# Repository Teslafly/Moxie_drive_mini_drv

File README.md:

# Moxie_drive_mini_drv
A motor drive based off https://github.com/vedderb/bldc-hardware using the drv8353 and toshiba fets

MoxiE-Drive - high power 12-75v motor controller
=============

design

Forged from the remminants of the oppressed vesc 6.
Raised on a diet of endless sphere and equals zero posts.
destined for a fight to the death in hilariously brutal Power Wheels Racing Series.
I give to you, the MoxiE-Drive.

This the Hardware for my derivitive of the Vesc-project.

## Schematic top level

## Layout -made with KiCad!-

## 3D views

Have a look at this post for a tutorial on how to get started:
http://vedder.se/2015/01/vesc-open-source-esc/

Made with KiCad 5

wonderfulfailure.wordpress.com

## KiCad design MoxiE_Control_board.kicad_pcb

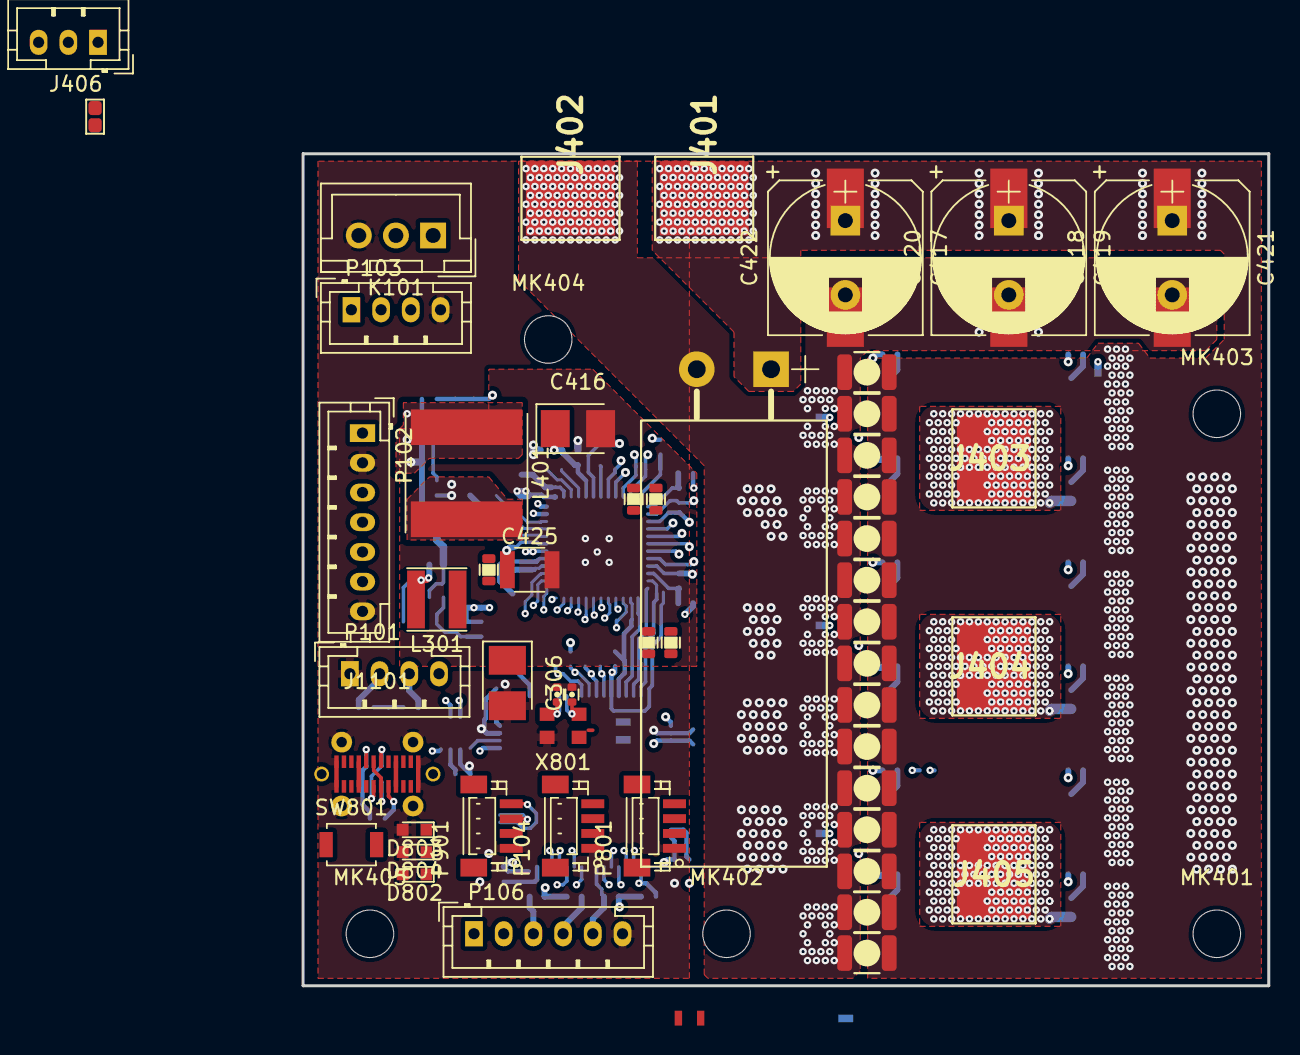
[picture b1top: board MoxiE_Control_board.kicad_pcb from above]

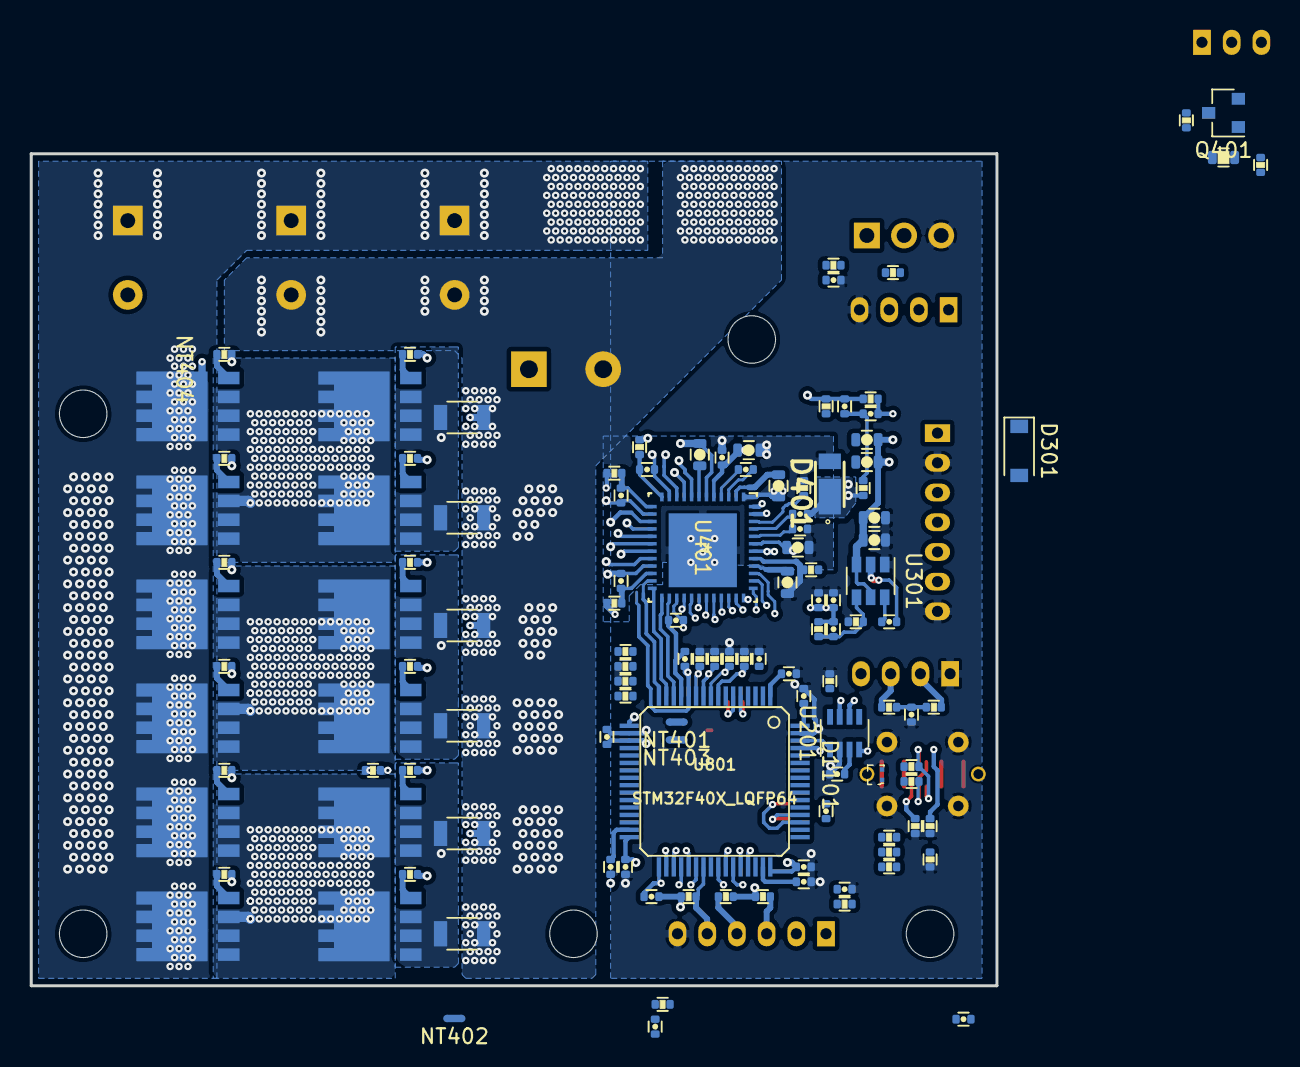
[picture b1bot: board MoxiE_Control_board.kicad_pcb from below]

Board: 4 copper layers, 65.0 x 56.0 mm, 187 parts (125 on the bottom side), 125 nets.

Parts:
C101, C102, C804: 100n; C_0402
C201: 4.7nf; C_0402
C202, C801, C802, C803, C805, C807, C809, C810, C811, C812: 2.2u; C_0402
C301, C308: 10uf; C_0603
C303, C423: 100nf; C_0402
C304, C305: 2.2uf; C_0402
C306: 100uf; CP_Tantalum_Case-B_EIA-3528-21_Reflow
C307: NP; C_0402
C401, C402, C413: 10uF; C_0603
C403, C410: 0.1uF; C_0402
C404: 0.1uF; C_0603
C405: 1uF; C_0402
C406: 2.2uF; C_0402
C407: 0.047uF; C_0402
C408, C409, C411: 1uF; C_0603
C412: 10nf; C_0402
C414: 560uF; CP_Radial_D12.5mm_P5.00mm_horiz
C415: 3nf; C_0402
C416: 10uf, 25v; CP_Tantalum_Case-B_EIA-3528-21_Reflow
C417, C419, C421: 56uF; CP_Radial_D10.0mm_P5.00mm
C418, C420, C422: 20uF; CP_Elec_10x10.5
C425, C502, C503, C504, C505, C506, C602, C603, C604, C605, C606, C702, C703, C704, C705, C706: 4.7uF; C_1210
C501, C601, C701: 2.2nF; C_0402
C806, C808: 15p; C_0402
D301: 1.5KExxA; D_SOD-123
D401: DFLS1100-7; POWERDI123_1
D802: BLUE; LED_0603
D803: GREEN; LED_0603
D804: RED; LED_0603
D1101: TPD2EUSB30DRTR; SOT-3
J101, J102: Conn_01x01; SMD_Pad_Array-1_Pitch1mm
J401: +Vbat; 1PAD_6x5mm
J402: Gnd; 1PAD_6x5mm
J403: A; 1PAD_6x5mm
J404: B; 1PAD_6x5mm
J405: C; 1PAD_6x5mm
J406: Conn_01x03; JST_PH_B3B-PH-K_03x2.00mm_Straight
J1101: USB_C_Receptacle; USB_C_receptacle_vertical
JP401: pwr_ctl_byp; J_0603
K101: SERVO; JST_XH_B03B-XH-A_03x2.50mm_Straight
L301: 4.7uH; L_Taiyo-Yuden_NR-40xx
L401: 470uH; L_wurth-8065
MK401, MK402, MK403, MK404, MK405: Mounting_Hole; MountingHole_3.2mm_M3_DIN965
NT401, NT402, NT403, NT404, NT503, NT603, NT703: Net-Tie_2; NetTie-2_SMD_Pad0.5mm
P101: CANBUS; JST_PH_B4B-PH-K_04x2.00mm_Straight
P102: CTRL_SIGNALS; JST_PH_B7B-PH-K_07x2.00mm_Straight
P103: Serial1/tim4; JST_PH_B4B-PH-K_04x2.00mm_Straight
P104, P901: I2C; JST_SH_BM04B-SRSS-TB_04x1.00mm_Straight
P106: HALL/Encoder; JST_PH_B6B-PH-K_06x2.00mm_Straight
P801: SWD_DEBUG; JST_SH_BM04B-SRSS-TB_04x1.00mm_Straight
Q401: Q_PNP_BCE; SOT-23
Q501, Q502, Q503, Q504, Q601, Q602, Q603, Q604, Q701, Q702, Q703, Q704: TPH2R608NH,L1Q; SOP8_Advance
R101: 0Ω; R_0402
R102, R105, R106, R501, R601, R701: 100Ω; R_0402
R103, R104: 100kΩ; R_0402
R107, R108, R109: 2k2Ω; R_0402
R110, R405, R416: 10kΩ; R_0402
R201, R202: 120R; R_0402
R203: 0R; R_0402
R302: R33.2k 0.1%; R_0402
R303: 10k 0.1%; R_0402
R401: 1kOhm; C_0402
R402: 10kΩ; C_0402
R403: 560kΩ; R_0402
R404: 200kΩ; R_0402
R406: 909Ω; R_0402
R407: 57.6kΩ; R_0402
R408, R410, R412, R414: 47kΩ; R_0603
R409, R411, R413, R415: 2.2kΩ; R_0402
R417: NTC 10kΩ; R_0402
R418: 1M; R_0402
R419: 500k; R_0603
R420: 100; R_0402
R421: 0Ω; R_0603
R502, R503, R504, R505, R602, R603, R604, R605, R702, R703, R704, R705: 5Ω; R_0402
R506, R507, R606, R607, R706, R707: 1mΩ; R_1206
R801, R802, R803, R804: 1k; R_0402
R1101, R1102: 22R; R_0402
R1103, R1104: 5.1k; R_0402
SW801: SW_Push; SW_SPST_B3U-1000P
U201: MAX3051; SOT-23-8
U301: TPS561201; SOT-23-6
U401: DRV8353RSRGZT; DRV8353RHRGZR
U801: STM32F40X_LQFP64; lqfp64_pad_mod
X801: 8MHz 10ppm; Oscillator_SMD_EuroQuartz_XO32-4pin_3.2x2.5mm

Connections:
+3.3VA: C406.1, C802.2, C805.2, NT403.1, U401.26, U801.13
+3V3: C202.1, C304.1, C305.1, C306.1, C307.1, C807.2, C809.2, C810.2, C811.2, C812.2, D301.1, L301.1, NT403.2, P102.1, P103.3, P104.2, P106.1, P901.2, R101.2, R107.2, R108.2, R109.2, R110.2, R302.1, R401.1, R402.1, R416.1, R801.2, SW801.2, U201.3, U801.1, U801.19, U801.32, U801.48, U801.64
+15V: C301.1, C308.1, C401.1, C402.1, C403.1, C413.1, C415.2, C416.1, L401.1, R405.1, R420.2, U301.3, U301.5, U401.5
+BATT: C414.1, C417.1, C418.1, C419.1, C420.1, C421.1, C422.1, C502.1, C503.1, C504.1, C505.1, C506.1, C602.1, C603.1, C604.1, C605.1, C606.1, C702.1, C703.1, C704.1, C705.1, C706.1, J401.1, JP401.1, NT404.1, Q401.3, Q501.1, Q503.1, Q601.1, Q603.1, Q701.1, Q703.1, R414.1, R418.1, R421.1
/ADC_BRAKE_R: P102.4, R106.2
/ADC_THROTTLE_R: P102.3, R105.2
/CAN_tranciever/CANH: P101.3, R201.1, U201.7
/CAN_tranciever/CANL: P101.2, R202.1, U201.6
/CAN_tranciever/CAN_RX: U201.4, U801.61
/CAN_tranciever/CAN_TX: U201.1, U801.62
/DRV_CLK: U401.31, U801.55
/DRV_CS: U401.32, U801.50
/DRV_MISO: R401.2, U401.29, U801.56
/DRV_MOSI: U401.30, U801.53
/Microcontroller/ADC_BRAKE: R104.1, R106.1, U801.21
/Microcontroller/ADC_TEMP: C423.1, R416.2, R417.1, U801.24
/Microcontroller/ADC_THROTTLE: R103.1, R105.1, U801.20
/Microcontroller/ADC_VBUS: R414.2, R415.1, U801.11
/Microcontroller/AUX1_PWM: J101.1, U801.22
/Microcontroller/AUX2_PWM: J102.1, U801.23
/Microcontroller/BOOT_0: R804.1, SW801.1, U801.60
/Microcontroller/BRAKE_SW: P102.6, U801.27
/Microcontroller/FAULT: R402.2, U401.28, U801.33
/Microcontroller/H1: U401.34, U801.41
/Microcontroller/H2: U401.36, U801.42
/Microcontroller/H3: U401.38, U801.43
/Microcontroller/HALL_1: P106.3, R107.1, U801.37
/Microcontroller/HALL_2: P106.4, R108.1, U801.38
/Microcontroller/HALL_3: P106.5, R109.1, U801.39
/Microcontroller/L1: U401.35, U801.34
/Microcontroller/L2: U401.37, U801.35
/Microcontroller/L3: U401.39, U801.36
/Microcontroller/LED_BL_R: D802.1, R801.1
/Microcontroller/LED_GN_R: D803.1, R802.1
/Microcontroller/LED_GREEN: R802.2, U801.57
/Microcontroller/LED_RD_R: D804.1, R803.1
/Microcontroller/LED_RED: R803.2, U801.54
/Microcontroller/REVERSE_SW: P102.5, U801.2
/Microcontroller/SCL_2: P104.4, U801.29
/Microcontroller/SDA_2: P104.3, U801.30
/Microcontroller/SERVO: C101.2, R102.1, U801.17
/Microcontroller/TEMP_MOTOR: C102.2, P106.2, R110.1, U801.25
/Microcontroller/USART1_RX: P103.1, U801.59
/Microcontroller/USART1_TX: P103.2, U801.58
/Microcontroller/VCAP1: C803.2, U801.31
/Microcontroller/VCAP2: C801.2, U801.47
/Microcontroller/XOSC_0: C806.1, U801.5, X801.2
/Microcontroller/XOSC_1: C808.1, U801.6, X801.1
/NRF/Bluetooth/BLE_RX: P901.4, U801.51
/NRF/Bluetooth/BLE_TX: P901.3, U801.52
/USB-C connector/D+: D1101.1, R1102.1, U801.45
/USB-C connector/D-: D1101.2, R1101.1, U801.44
/drv_power_stage/A_ISENSE: U401.25, U801.14
/drv_power_stage/A_VSENSE: R408.2, R409.1, U801.8
/drv_power_stage/BK_BST_C: C410.1, U401.45
/drv_power_stage/BK_RT_SD: R403.2, U401.47
/drv_power_stage/BK_SW: C410.2, D401.1, L401.2, R407.2, U401.42
/drv_power_stage/BK_VCC: C405.1, U401.44
/drv_power_stage/BK_VIN: C404.1, C425.1, R403.1, R421.2, U401.43
/drv_power_stage/B_ISENSE: U401.24, U801.15
/drv_power_stage/B_VSENSE: R410.2, R411.1, U801.9
/drv_power_stage/C_ISENSE: U401.23, U801.16
/drv_power_stage/C_VSENSE: R412.2, R413.1, U801.10
/drv_power_stage/ENABLE: U401.33, U801.40
/drv_power_stage/GDRV_VSENSE: C412.1, R405.2, R406.1, U401.48, U801.26
/drv_power_stage/PHASE_A: J403.1, Q701.3, Q702.1, Q703.3, Q704.1, R408.1, U401.9
/drv_power_stage/PHASE_B: J404.1, Q601.3, Q602.1, Q603.3, Q604.1, R410.1, U401.16
/drv_power_stage/PHASE_C: J405.1, Q501.3, Q502.1, Q503.3, Q504.1, R412.1, U401.19
/drv_power_stage/batt_pwr_ctl: JP401.2, Q401.2
/drv_power_stage/buck_rcl: R404.2, U401.46
/drv_power_stage/dvdd: C409.1, U401.40
/drv_power_stage/power_phase_A/H_GATE: R702.2, R704.2, U401.8
/drv_power_stage/power_phase_A/L_GATE: R703.2, R705.2, U401.10
/drv_power_stage/power_phase_A/NR_SENSE: C701.1, R701.1, U401.12
/drv_power_stage/power_phase_A/NR_SENSE_R: NT703.1, R701.2
/drv_power_stage/power_phase_A/PR_SENSE: C701.2, Q702.3, Q704.3, R706.1, R707.1, U401.11
/drv_power_stage/power_phase_B/H_GATE: R602.2, R604.2, U401.17
/drv_power_stage/power_phase_B/L_GATE: R603.2, R605.2, U401.15
/drv_power_stage/power_phase_B/NR_SENSE: C601.1, R601.1, U401.13
/drv_power_stage/power_phase_B/NR_SENSE_R: NT603.1, R601.2
/drv_power_stage/power_phase_B/PR_SENSE: C601.2, Q602.3, Q604.3, R606.1, R607.1, U401.14
/drv_power_stage/power_phase_C/H_GATE: R502.2, R504.2, U401.18
/drv_power_stage/power_phase_C/L_GATE: R503.2, R505.2, U401.20
/drv_power_stage/power_phase_C/NR_SENSE: C501.1, R501.1, U401.22
/drv_power_stage/power_phase_C/NR_SENSE_R: NT503.1, R501.2
/drv_power_stage/power_phase_C/PR_SENSE: C501.2, Q502.3, Q504.3, R506.1, R507.1, U401.21
/drv_power_stage/pwr_ctl: J406.3, R419.2
/drv_power_stage/pwr_ctl_g: Q401.1, R418.2, R419.1
/drv_power_stage/sw_led: J406.1, R420.1
/drv_power_stage/vcp: C411.2, U401.7
/drv_power_stage/vdrain: C411.1, NT404.2, U401.6
/drv_power_stage/vgls: C408.2, U401.2
GND: C101.1, C102.1, C201.2, C202.2, C301.2, C304.2, C305.2, C306.2, C308.2, C409.2, C423.2, C801.1, C803.1, C804.1, C806.2, C807.1, C808.2, C809.1, C810.1, C811.1, C812.1, D301.2, D802.2, D803.2, D804.2, D1101.3, J1101.A1, J1101.A12, J1101.B1, J1101.B12, J1101.S1, K101.3, NT401.2, NT402.2, P101.1, P102.2, P102.7, P103.4, P104.1, P106.6, P801.1, P901.1, R103.2, R104.2, R203.2, R303.2, R409.2, R411.2, R413.2, R415.2, R804.2, R1103.2, R1104.2, U201.2, U301.1, U401.41, U801.18, U801.63, X801.3
GNDA: C406.2, C802.1, C805.1, NT401.1, U401.27, U801.12
GNDD: C401.2, C402.2, C403.2, C404.2, C405.2, C408.1, C413.2, C414.2, C416.2, C417.2, C418.2, C419.2, C420.2, C421.2, C422.2, C425.2, C502.2, C503.2, C504.2, C505.2, C506.2, C602.2, C603.2, C604.2, C605.2, C606.2, C702.2, C703.2, C704.2, C705.2, C706.2, D401.2, J402.1, J406.2, NT402.1, NT503.2, NT603.2, NT703.2, R404.1, R406.2, R417.2, R506.2, R507.2, R606.2, R607.2, R706.2, R707.2, U401.1, U401.49
NRST: C804.2, P801.2, U801.7
unnamed: C201.1, R201.2, R202.2
unnamed: C303.1, L301.2, U301.2
unnamed: C303.2, U301.6
unnamed: C307.2, R302.2, R303.1, U301.4
unnamed: C407.1, U401.4
unnamed: C407.2, U401.3
unnamed: C412.2, C415.1, R407.1
unnamed: J1101.A4, J1101.A9, J1101.B4, J1101.B9
unnamed: J1101.A5, R1104.1
unnamed: J1101.A6, J1101.B6, R1102.2
unnamed: J1101.A7, J1101.B7, R1101.2
unnamed: J1101.B5, R1103.1
unnamed: K101.1, R102.2
unnamed: K101.2, R101.1
unnamed: Q501.2, R502.1
unnamed: Q502.2, R503.1
unnamed: Q503.2, R504.1
unnamed: Q504.2, R505.1
unnamed: Q601.2, R602.1
unnamed: Q602.2, R603.1
unnamed: Q603.2, R604.1
unnamed: Q604.2, R605.1
unnamed: Q701.2, R702.1
unnamed: Q702.2, R703.1
unnamed: Q703.2, R704.1
unnamed: Q704.2, R705.1
unnamed: R203.1, U201.8
SWCLK: P801.4, U801.49
SWDIO: P801.3, U801.46

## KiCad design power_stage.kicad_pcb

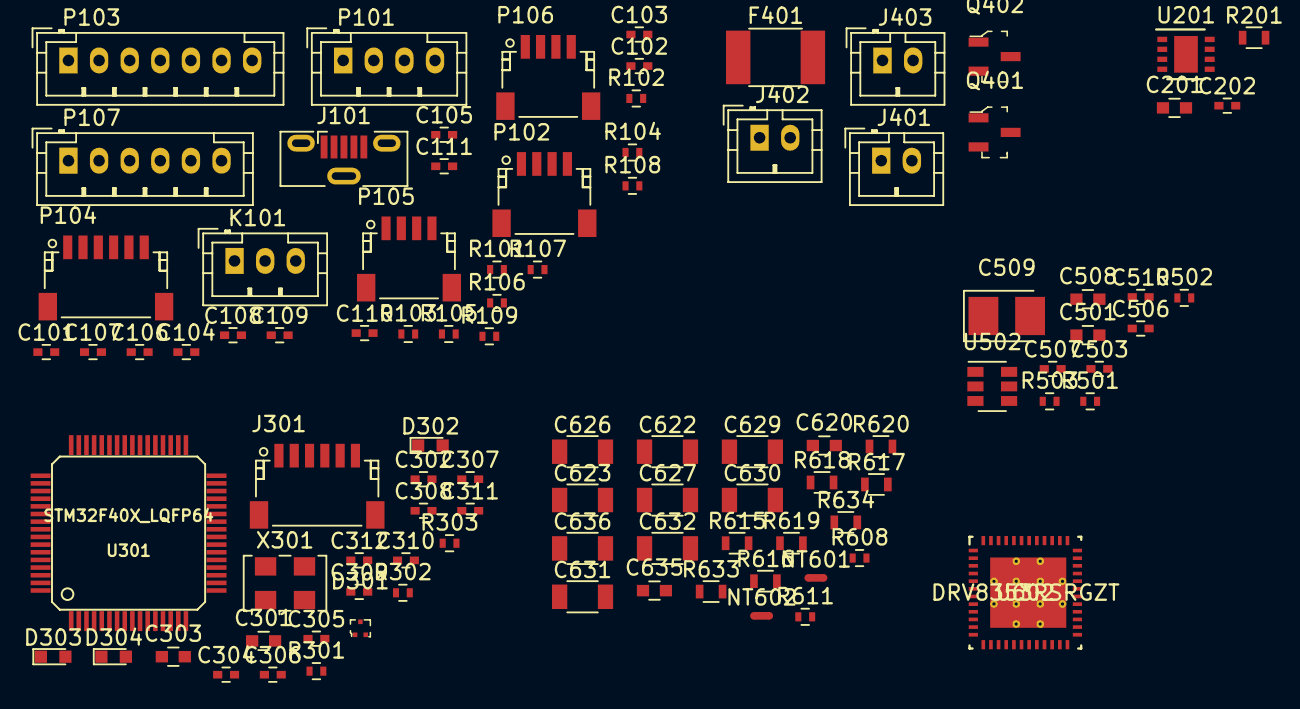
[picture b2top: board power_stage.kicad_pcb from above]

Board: 2 copper layers, 96 parts (0 on the bottom side), 69 nets, no tracks yet.

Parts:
C101, C110, C304: 100n; C_0402
C102, C106, C107, C108, C109, C111, C202, C503, C506, C507: 100nf; C_0402
C103, C104, C105: 4.7nf; C_0402
C201, C301, C303: 2.2u; C_0603
C302, C305, C307, C309, C310, C311, C312: 2.2u; C_0402
C306, C308: 15p; C_0402
C501, C508: 2.2uf; C_0603
C509: 100uf; CP_Tantalum_Case-B_EIA-3528-21_Reflow
C510: NP; C_0402
C620, C635: 1uf; C_0603
C622, C623, C626, C627, C629, C630, C631, C632, C636: 100v_1.0uF; C_1206
D301: TPD2EUSB30DRTR; SOT-3
D302: BLUE; LED_0603
D303: GREEN; LED_0603
D304: RED; LED_0603
F401: 0.5A polyfuse; R_1812
J101: USB_B_Micro; USB_Micro-B_Vertical_Molex-105133-0001
J301: SWD; JST_SH_SM06B-SRSS-TB_06x1.00mm_Angled
J401, J402, J403: Conn_01x02; JST_PH_B2B-PH-K_02x2.00mm_Straight
K101: SERVO; JST_PH_B3B-PH-K_03x2.00mm_Straight
NT601, NT602: Net-Tie_2; NetTie-2_SMD_Pad0.5mm
P101: CANBUS; JST_PH_B4B-PH-K_04x2.00mm_Straight
P102: Serial3; JST_SH_SM04B-SRSS-TB_04x1.00mm_Angled
P103: CTRL_SIGNALS; JST_PH_B7B-PH-K_07x2.00mm_Straight
P104: SPI; JST_SH_SM06B-SRSS-TB_06x1.00mm_Angled
P105: Serial1/tim4; JST_SH_SM04B-SRSS-TB_04x1.00mm_Angled
P106: I2C; JST_SH_SM04B-SRSS-TB_04x1.00mm_Angled
P107: HALL/Encoder; JST_PH_B6B-PH-K_06x2.00mm_Straight
Q401, Q402: IRLML6344TRPBF; SOT-23-3
R101: 100R; R_0402
R102, R103: 100k; R_0402
R104, R105: 22R; R_0402
R106, R107, R108, R608, R611: 2k2; R_0402
R109: 10k; R_0402
R201: 220R; R_0603
R301, R302, R303, R501: 1k; R_0402
R502: R33.2k 0.1%; R_0402
R503: 10k 0.1%; R_0402
R615, R616, R617, R618, R619, R620: 10R; R_0603
R633: 39k; R_0603
R634: 2k2; R_0603
U201: TJA1051TK-3; DFN-8-1EP_3x3mm_Pitch0.65mm
U301: STM32F40X_LQFP64; lqfp64_pad_mod
U502: TPS561201; SOT-23-6
U602: DRV8353RSRGZT; DRV8353RHRGZR
X301: 8MHz 10ppm; Oscillator_SMD_EuroQuartz_XO53-4pin_5.0x3.2mm

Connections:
+3V3: C202.1, C302.2, C305.2, C307.2, C309.2, C310.2, C311.2, C312.2, C507.1, C508.1, C509.1, C510.1, J301.1, P102.3, P103.1, P104.1, P105.3, P106.3, P107.1, R106.2, R107.2, R108.2, R109.2, R301.2, R502.1, U201.5, U301.1, U301.13, U301.19, U301.32, U301.48, U301.64, U602.26
+5V: C201.1, U201.3
+12V: C501.1, C503.1, C620.1, F401.1, R501.2, U502.3
+BATT: U602.6, U602.43
/12vbuck_SENSE: C111.1, U301.21
/PHASE_CURRENT_1_ADC: C103.1, U301.8
/PHASE_CURRENT_2_ADC: C104.1, U301.9
/PHASE_CURRENT_3_ADC: C105.1, U301.10
/PHASE_V_1_ADC: C107.1, U301.14
/PHASE_V_2_ADC: C108.1, U301.15
/PHASE_V_3_ADC: C109.1, U301.16
/aux_outputs/AUX1_PWM: Q401.1, U301.22
/aux_outputs/AUX2_PWM: Q402.1, U301.23
/drv_power_stage/EN0: U602.35, U602.37, U602.39
/drv_power_stage/HG: R616.2, R617.2, R619.2
/drv_power_stage/LG: R615.2, R618.2, R620.2
/drv_power_stage/PHASE_R: C635.2, R633.2
/drv_power_stage/PHASE_V_SENSE: R633.1, R634.1
/sheet5B3977DF/CANH: P101.3, R201.1, U201.7
/sheet5B3977DF/CANL: P101.2, R201.2, U201.6
/sheet5B3977DF/CAN_RX: U201.4, U301.61
/sheet5B3977DF/CAN_TX: U201.1, U301.62
/sheet5B3977E0/ADC_BRAKE: P103.4, R103.1, U301.27
/sheet5B3977E0/ADC_TEMP: C102.1, U301.24
/sheet5B3977E0/ADC_THROTTLE: P103.3, R102.1, U301.26
/sheet5B3977E0/ADC_VBUS: C106.1, U301.11
/sheet5B3977E0/HALL_1: P107.3, R106.1, U301.37
/sheet5B3977E0/HALL_2: P107.4, R107.1, U301.38
/sheet5B3977E0/HALL_3: P107.5, R108.1, U301.39
/sheet5B3977E0/LED_GREEN: R302.2, U301.3
/sheet5B3977E0/LED_RED: R303.2, U301.4
/sheet5B3977E0/SCL_2: P106.1, U301.29
/sheet5B3977E0/SDA_2: P106.2, U301.30
/sheet5B3977E0/SERVO: C101.2, R101.1, U301.17
/sheet5B3977E0/SPI3_MISO: P104.3, U301.56
/sheet5B3977E0/SPI3_MOSI: P104.2, U301.53
/sheet5B3977E0/SPI3_NSS: P104.5, U301.50
/sheet5B3977E0/SPI3_SCK: P104.4, U301.55
/sheet5B3977E0/TEMP_MOTOR: C110.2, P107.2, R109.1, U301.25
/sheet5B3977E0/USART1_RX: P105.1, U301.59
/sheet5B3977E0/USART1_TX: P105.2, U301.58
/sheet5B3977E0/USART3_RX: P102.1, U301.52
/sheet5B3977E0/USART3_TX: P102.2, U301.51
/sheet5B3977E0/USB_DM: D301.2, R105.1, U301.44
/sheet5B3977E0/USB_DP: D301.1, R104.1, U301.45
/sheet5B3977E0/VCAP1: C303.2, U301.31
/sheet5B3977E0/VCAP2: C301.2, U301.47
GND: C101.1, C102.2, C103.2, C104.2, C105.2, C106.2, C107.2, C108.2, C109.2, C110.1, C111.2, C201.2, C202.2, C301.1, C302.1, C303.1, C304.1, C305.1, C306.2, C307.1, C308.2, C309.1, C310.1, C311.1, C312.1, C501.2, C503.2, C507.2, C508.2, C509.2, D301.3, D302.2, D303.2, D304.2, J101.5, J101.6, J301.3, K101.3, NT601.2, NT602.1, P101.1, P102.4, P103.2, P103.7, P104.6, P105.4, P106.4, P107.6, R102.2, R103.2, R503.2, R608.2, R611.2, R634.2, U201.2, U201.8, U201.9, U301.12, U301.18, U301.60, U301.63, U502.1, X301.3
GNDD: NT601.1, U602.1, U602.27, U602.41, U602.49
GNDPWR: C620.2, C622.2, C623.2, C626.2, C627.2, C629.2, C630.2, C631.2, C632.2, C636.2, J403.2, NT602.2, Q401.2, Q402.2
NRST: C304.2, J301.5, U301.7
unnamed: C306.1, U301.5, X301.1
unnamed: C308.1, U301.6, X301.2
unnamed: C506.1, U502.2
unnamed: C506.2, U502.6
unnamed: C510.2, R502.2, R503.1, U502.4
unnamed: D302.1, R301.1
unnamed: D303.1, R302.1
unnamed: D304.1, R303.1
unnamed: F401.2, J401.1, J402.1, J403.1
unnamed: J101.2, R105.2
unnamed: J101.3, R104.2
unnamed: J401.2, Q401.3
unnamed: J402.2, Q402.3
unnamed: K101.1, R101.2
unnamed: R501.1, U502.5
SWCLK: J301.2, U301.49
SWDIO: J301.4, U301.46
VBUS: C622.1, C623.1, C626.1, C627.1, C629.1, C630.1, C631.1, C632.1, C636.1

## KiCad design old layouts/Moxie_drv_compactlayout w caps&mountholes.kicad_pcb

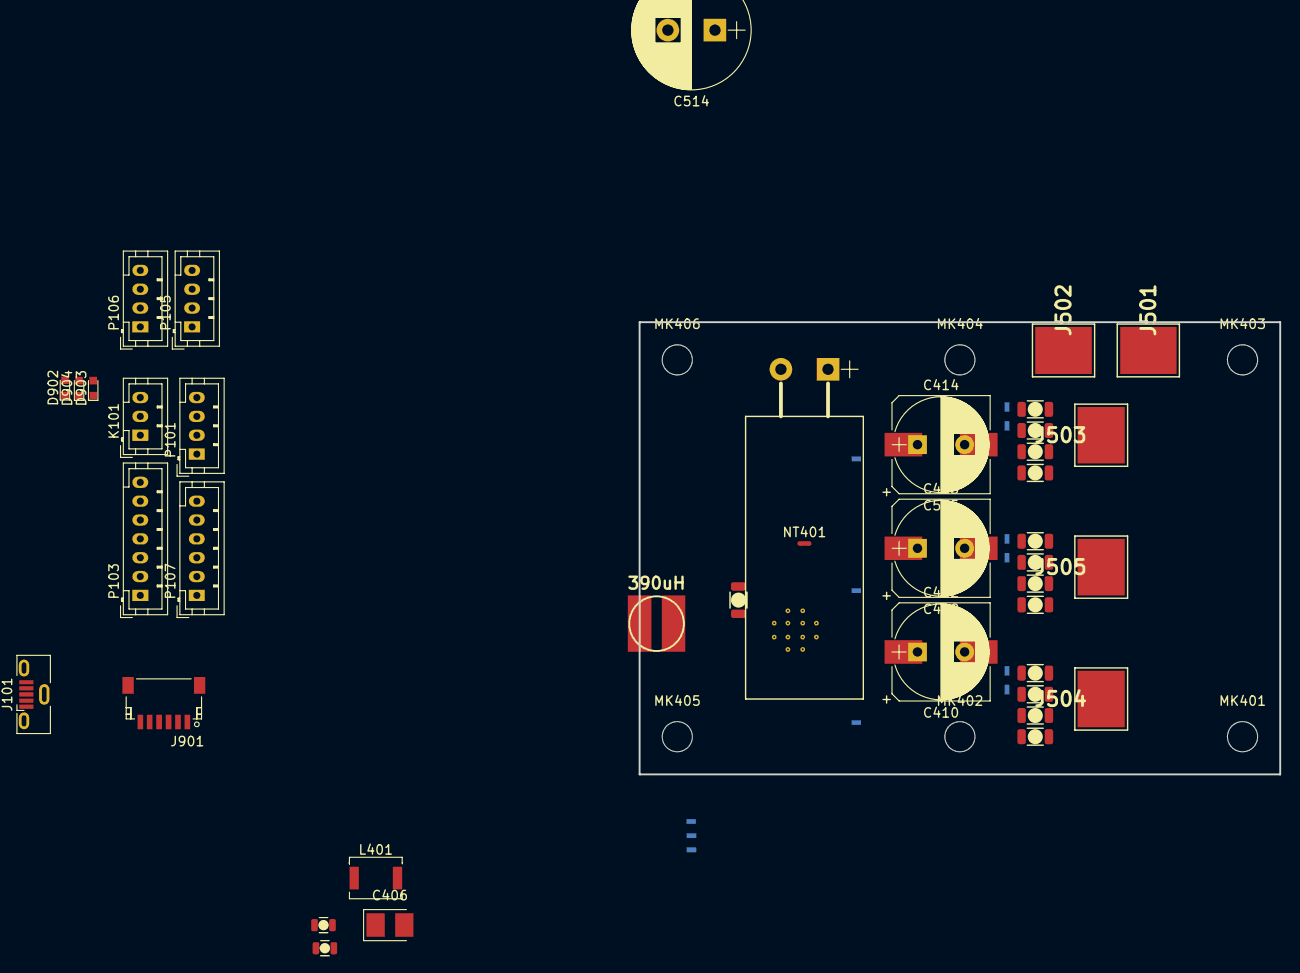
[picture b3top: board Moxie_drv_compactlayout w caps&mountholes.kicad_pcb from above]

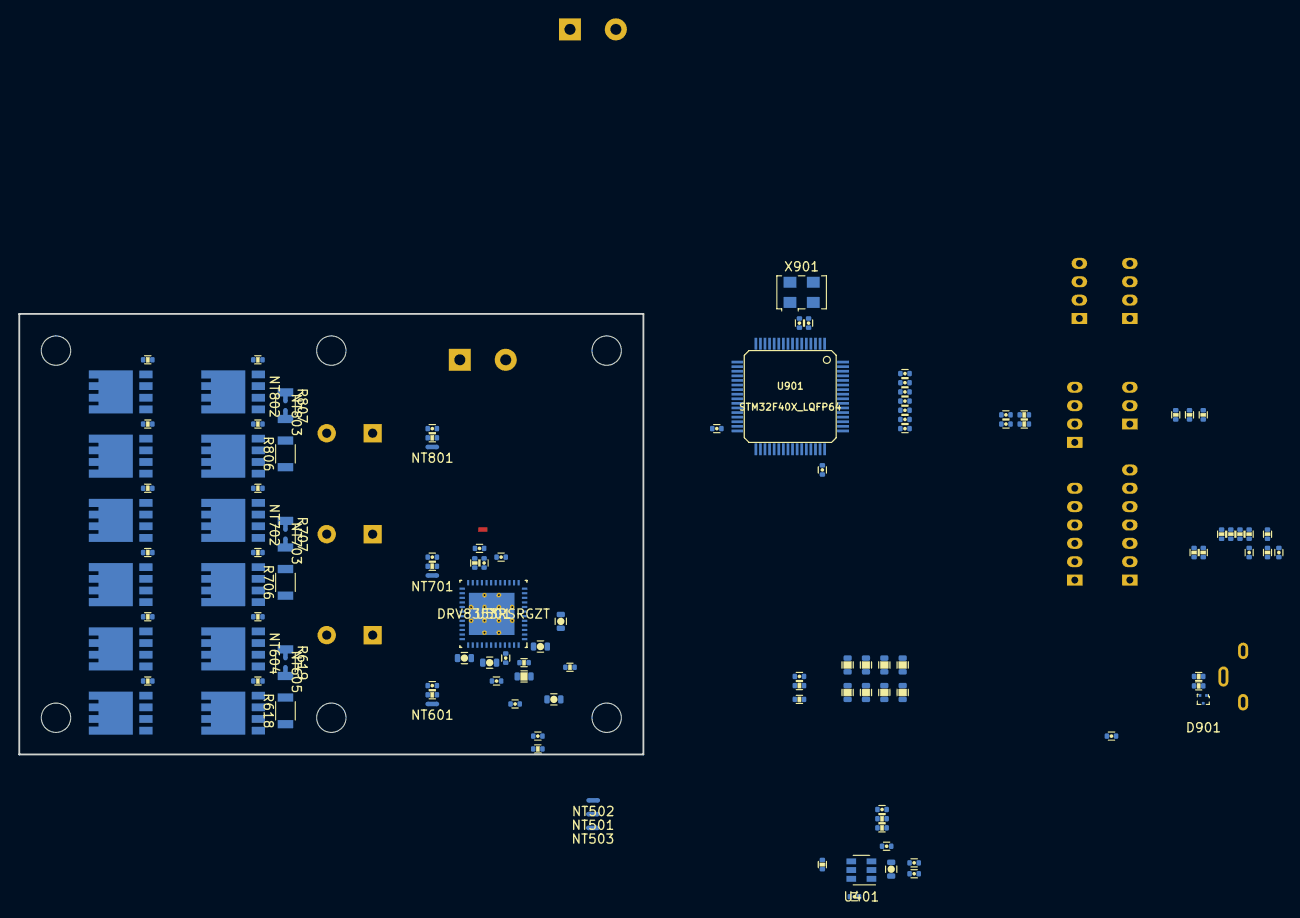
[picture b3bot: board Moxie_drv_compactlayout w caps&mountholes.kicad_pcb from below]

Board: 4 copper layers, 68.0 x 48.0 mm, 170 parts (121 on the bottom side), 110 nets, no tracks yet.

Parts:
C101, C107, C904: 100n; C_0402
C201: 4.7nf; C_0402
C202, C901, C902, C903, C905, C907, C909, C910, C911, C912: 2.2u; C_0402
C401: 2.2uf; C_0603
C402, C403, C404, C408: 100nf; C_0402
C405: 2.2uf; C_0402
C406: 100uf; CP_Tantalum_Case-B_EIA-3528-21_Reflow
C407: NP; C_0402
C409, C410, C515: 20uF; CP_Elec_10x10.5
C411: 560uF; CP_Radial_D12.5mm_P5.00mm_horiz
C412, C413, C414: 56uF; CP_Radial_D10.0mm_P5.00mm
C501: 10uF; C_0805
C502: 1.5uF; C_1206
C503, C504: 0.1uF; C_0603
C505: 0.47uF; C_0402
C506: 0.1uF; C_0402
C507: 0.047uF; C_0402
C508, C509, C511: 1uF; C_0603
C510: 0.01uF; C_0402
C512: 18nF; C_0402
C513: 22uF; C_0805
C514: 560uF; CP_Radial_D12.5mm_P5.00mm
C601, C701, C801: 2.2nF; C_0402
C602, C603, C604, C606, C702, C703, C704, C706, C802, C803, C804, C806: 1uF; C_1206
C906, C908: 15p; C_0402
D901: TPD2EUSB30DRTR; SOT-3
D902: BLUE; LED_0603
D903: GREEN; LED_0603
D904: RED; LED_0603
J101: USB_B_Micro; USB_Micro-B_Vertical_Molex-105133-0001
J501: +Vbat; 1PAD_6x5mm
J502: Gnd; 1PAD_6x5mm
J503: A; 1PAD_6x5mm
J504: B; 1PAD_6x5mm
J505: C; 1PAD_6x5mm
J901: SWD; JST_SH_SM06B-SRSS-TB_06x1.00mm_Angled
K101: SERVO; JST_PH_B3B-PH-K_03x2.00mm_Straight
L401: 3.3uH; L_Neosid_Ms42
L501: 390uH; inductor_smd_5.8mmx4.8hmm
MK401, MK402, MK403, MK404, MK405, MK406: Mounting_Hole; MountingHole_3.2mm_M3_DIN965
NT401, NT501, NT502, NT503, NT601, NT604, NT605, NT701, NT702, NT703, NT801, NT802, NT803: Net-Tie_2; NetTie-2_SMD_Pad0.5mm
P101: CANBUS; JST_PH_B4B-PH-K_04x2.00mm_Straight
P103: CTRL_SIGNALS; JST_PH_B7B-PH-K_07x2.00mm_Straight
P105: Serial1/tim4; JST_PH_B4B-PH-K_04x2.00mm_Straight
P106: I2C; JST_PH_B4B-PH-K_04x2.00mm_Straight
P107: HALL/Encoder; JST_PH_B6B-PH-K_06x2.00mm_Straight
Q601, Q602, Q603, Q604, Q701, Q702, Q703, Q704, Q801, Q802, Q803, Q804: TPH2R608NH,L1Q; SOP8_Advance
R101: 0Ω; R_0402
R102, R603, R703, R803: 100Ω; R_0402
R103, R104: 100kΩ; R_0402
R105, R106: 22R; R_0402
R107, R108, R109: 2k2Ω; R_0402
R110, R516: 10kΩ; R_0402
R201, R202: 120R; R_0402
R401, R901, R902, R903: 1k; R_0402
R402: R33.2k 0.1%; R_0402
R403: 10k 0.1%; R_0402
R501: 1kOhm; C_0402
R502: 10kΩ; C_0402
R503: 560kΩ; R_0402
R504: 200kΩ; R_0402
R505: 5.1kΩ; R_0402
R506: 1.0kΩ; R_0402
R507: 910mΩ; R_0603
R508, R510, R512, R514: 47kΩ; R_0603
R509, R511, R513, R515: 2.2kΩ; R_0603
R517: NTC 10kΩ; R_0402
R601, R602, R604, R605, R701, R702, R704, R705, R801, R802, R804, R805: 5Ω; R_0402
R618, R619, R706, R707, R806, R807: 1mΩ; R_1206
U401: TPS561201; SOT-23-6
U501: DRV8353RSRGZT; DRV8353RHRGZR
U901: STM32F40X_LQFP64; lqfp64_pad_mod
X901: 8MHz 10ppm; Oscillator_SMD_EuroQuartz_XO53-4pin_5.0x3.2mm

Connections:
+3V3: C202.1, C404.1, C405.1, C406.1, C407.1, C902.2, C905.2, C907.2, C909.2, C910.2, C911.2, C912.2, J901.1, L401.1, NT503.2, P103.1, P105.3, P106.3, P107.1, R101.2, R107.2, R108.2, R109.2, R110.2, R402.1, R501.1, R502.1, R516.1, R901.2, U901.1, U901.13, U901.19, U901.32, U901.48, U901.64
+12V: C401.1, C402.1, C501.1, C503.1, C513.1, R401.2, R507.2, U401.3, U501.5
+BATT: C409.1, C410.1, C411.1, C412.1, C413.1, C414.1, C502.1, C504.1, C514.1, C515.1, C602.1, C603.1, C604.1, C606.1, C702.1, C703.1, C704.1, C706.1, C802.1, C803.1, C804.1, C806.1, J501.1, NT401.1, Q601.1, Q603.1, Q701.1, Q703.1, Q801.1, Q803.1, R503.1, R514.1, U501.43
/CAN_tranciever/CANH: P101.3, R201.1
/CAN_tranciever/CANL: P101.2, R202.1
/Microcontroller/ADC_BRAKE: P103.4, R104.1, U901.27
/Microcontroller/ADC_TEMP: C408.1, R516.2, R517.1, U901.24
/Microcontroller/ADC_THROTTLE: P103.3, R103.1, U901.26
/Microcontroller/ADC_VBUS: R514.2, R515.1, U901.11
/Microcontroller/BRAKE_SW: P103.6, U901.57
/Microcontroller/FAULT: R502.2, U501.28, U901.33
/Microcontroller/H1: U501.34, U901.41
/Microcontroller/H2: U501.36, U901.42
/Microcontroller/H3: U501.38, U901.43
/Microcontroller/HALL_1: P107.3, R107.1, U901.37
/Microcontroller/HALL_2: P107.4, R108.1, U901.38
/Microcontroller/HALL_3: P107.5, R109.1, U901.39
/Microcontroller/L1: U501.35, U901.34
/Microcontroller/L2: U501.37, U901.35
/Microcontroller/L3: U501.39, U901.36
/Microcontroller/LED_GREEN: R902.2, U901.3
/Microcontroller/LED_RED: R903.2, U901.4
/Microcontroller/SCL_2: P106.1, U901.29
/Microcontroller/SDA_2: P106.2, U901.30
/Microcontroller/SERVO: C101.2, R102.1, U901.17
/Microcontroller/TEMP_MOTOR: C107.2, P107.2, R110.1, U901.25
/Microcontroller/USART1_RX: P105.1, U901.59
/Microcontroller/USART1_TX: P105.2, U901.58
/Microcontroller/USB_DM: D901.2, R106.1, U901.44
/Microcontroller/USB_DP: D901.1, R105.1, U901.45
/Microcontroller/VCAP1: C903.2, U901.31
/Microcontroller/VCAP2: C901.2, U901.47
/drv_power_stage/3.3_IREF: C506.1, NT503.1, U501.26
/drv_power_stage/A_ISENSE: U501.25, U901.8
/drv_power_stage/A_VSENSE: R508.2, R509.1, U901.14
/drv_power_stage/B_ISENSE: U501.24, U901.9
/drv_power_stage/B_VSENSE: R510.2, R511.1, U901.15
/drv_power_stage/C_ISENSE: U501.23, U901.10
/drv_power_stage/C_VSENSE: R512.2, R513.1, U901.16
/drv_power_stage/DRV_SDO: R501.2, U501.29
/drv_power_stage/ENABLE: U501.33, U901.40
/drv_power_stage/GDRV_VSENSE: C512.1, R505.2, R506.1, U501.48
/drv_power_stage/PHASE_A: J503.1, NT801.2, Q801.3, Q802.1, Q803.3, Q804.1, R508.1
/drv_power_stage/PHASE_B: J504.1, NT601.2, Q601.3, Q602.1, Q603.3, Q604.1, R510.1
/drv_power_stage/PHASE_C: J505.1, NT701.2, Q701.3, Q702.1, Q703.3, Q704.1, R512.1
/drv_power_stage/buck_rcl: R504.2, U501.46
/drv_power_stage/power_phase_A/H_GATE: R801.2, R804.2, U501.8
/drv_power_stage/power_phase_A/H_SWITCH: NT801.1, U501.9
/drv_power_stage/power_phase_A/L_GATE: R802.2, R805.2, U501.10
/drv_power_stage/power_phase_A/NR_SENSE: C801.1, R803.1, U501.12
/drv_power_stage/power_phase_A/PH_GND_LOW: NT802.2, Q802.3, Q804.3, R806.1, R807.1
/drv_power_stage/power_phase_A/PR_SENSE: C801.2, NT802.1, U501.11
/drv_power_stage/power_phase_B/H_GATE: R601.2, R604.2, U501.17
/drv_power_stage/power_phase_B/H_SWITCH: NT601.1, U501.16
/drv_power_stage/power_phase_B/L_GATE: R602.2, R605.2, U501.15
/drv_power_stage/power_phase_B/NR_SENSE: C601.1, R603.1, U501.13
/drv_power_stage/power_phase_B/PH_GND_LOW: NT604.2, Q602.3, Q604.3, R618.1, R619.1
/drv_power_stage/power_phase_B/PR_SENSE: C601.2, NT604.1, U501.14
/drv_power_stage/power_phase_C/H_GATE: R701.2, R704.2, U501.18
/drv_power_stage/power_phase_C/H_SWITCH: NT701.1, U501.19
/drv_power_stage/power_phase_C/L_GATE: R702.2, R705.2, U501.20
/drv_power_stage/power_phase_C/NR_SENSE: C701.1, R703.1, U501.22
/drv_power_stage/power_phase_C/PH_GND_LOW: NT702.2, Q702.3, Q704.3, R706.1, R707.1
/drv_power_stage/power_phase_C/PR_SENSE: C701.2, NT702.1, U501.21
GND: C101.1, C107.1, C201.2, C202.2, C401.2, C402.2, C404.2, C405.2, C406.2, C409.2, C410.2, C411.2, C412.2, C413.2, C414.2, C514.2, C515.2, C901.1, C903.1, C904.1, C906.2, C907.1, C908.2, C909.1, C910.1, C911.1, C912.1, D901.3, D902.2, D903.2, D904.2, J101.5, J101.6, J502.1, J901.3, K101.3, NT501.2, NT502.2, P101.1, P103.2, P103.7, P105.4, P106.4, P107.6, R103.2, R104.2, R403.2, U401.1, U501.41, U901.18, U901.60, U901.63, X901.3
GNDA: C408.2, C506.2, C902.1, C905.1, NT501.1, U501.27, U901.12
GNDD: C501.2, C502.2, C503.2, C504.2, C505.2, C508.1, C509.2, C513.2, C602.2, C603.2, C604.2, C606.2, C702.2, C703.2, C704.2, C706.2, C802.2, C803.2, C804.2, C806.2, NT502.1, NT605.2, NT703.2, NT803.2, R504.1, R506.2, R509.2, R511.2, R513.2, R515.2, R517.2, R618.2, R619.2, R706.2, R707.2, R806.2, R807.2, U501.1, U501.49
NRST: C904.2, J901.5, U901.7
unnamed: C201.1, R201.2, R202.2
unnamed: C403.1, L401.2, U401.2
unnamed: C403.2, U401.6
unnamed: C407.2, R402.2, R403.1, U401.4
unnamed: C505.1, U501.44
unnamed: C507.1, U501.4
unnamed: C507.2, U501.3
unnamed: C508.2, U501.2
unnamed: C509.1, U501.40
unnamed: C510.1, U501.45
unnamed: C510.2, L501.2, U501.42
unnamed: C511.1, NT401.2, U501.6
unnamed: C511.2, U501.7
unnamed: C512.2, L501.1, R505.1, R507.1
unnamed: C906.1, U901.5, X901.1
unnamed: C908.1, U901.6, X901.2
unnamed: D902.1, R901.1
unnamed: D903.1, R902.1
unnamed: D904.1, R903.1
unnamed: J101.2, R106.2
unnamed: J101.3, R105.2
unnamed: K101.1, R102.2
unnamed: K101.2, R101.1
unnamed: NT605.1, R603.2
unnamed: NT703.1, R703.2
unnamed: NT803.1, R803.2
unnamed: Q601.2, R601.1
unnamed: Q602.2, R602.1
unnamed: Q603.2, R604.1
unnamed: Q604.2, R605.1
unnamed: Q701.2, R701.1
unnamed: Q702.2, R702.1
unnamed: Q703.2, R704.1
unnamed: Q704.2, R705.1
unnamed: Q801.2, R801.1
unnamed: Q802.2, R802.1
unnamed: Q803.2, R804.1
unnamed: Q804.2, R805.1
unnamed: R401.1, U401.5
unnamed: R503.2, U501.47
SWCLK: J901.2, U901.49
SWDIO: J901.4, U901.46

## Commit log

2019-08-03 initial WIP for the moxie drive mini with drv
2019-08-03 updated readme and used updated 3.3v can controller since there is no 5v rail
2019-12-04 further progress finalising schematic and power stage laied out. drv is fanned out, and logic is starting to be routed
2020-01-12 connector layout basically finalised. drv gate layout finished mcu layout starting
2020-01-31 pre pin refactor/remap incremental commit

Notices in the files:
parts and their libraries:
Copyright 2016 Accelerated Designs. All rights reserved.
